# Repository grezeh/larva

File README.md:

# larva
larva keyboard related sketches, materials, etc

# larva mk.2

Mk.3 options:

 Larva keyboard is designed as part of a personal platform for research 
of combined, adaptable, extended latin+cyrillic keymap and layout with better ergonomics for day-to-day use.

 Keyboards, keymap, layouts are developed concurrently, work in symbiosis.
I name the whole research project "mnemoNИk|Kombine". 

 Larva PCB+custom plate fits in "daisy40% hhkb" keyboard case by Kprepublic.
Larva mk1 has 4 through-hole LED positions, no rgb, uses *AU mcu.

Mk2 has in addition 2 rgb smd LED slots for up-facing SK6812MINI-E LEDs 
and 2 pre-assembled mono-color smd LEDs as alternative to 2 lower through-hole LEDs(facedown, was an experimental feature)
and a few small QoL improvements. 

Mk2.1-light version cuts rgb and goes open-source. Pcbs routed by MarvFPV

Mk.3 pcb outline made smaller, to additionally fit "poseidon40" case by kprepublic. Added one more bottom row option and total-non-stab option (without iso enter). Modded by JLW, according to my specs (will see after the proto-run, how were the assumptions).

Current software-side implementation consists of QMK/vial +custom Windows keymap (needs updating).

Default keymap is basic latin+ numpad keycodes (looks chaotic, but gives more possibilities to reprogam); top-mid led is programmed as Num.Lock and it's engaged (put your novelties there and light them up; engaged numlock enables better bottom row options).

 For activating the bootloader: press the RST button on the back of the pcb.

 (The keyboard design line is constantly evolving, can differ in shapes and sizes, but all serve the same ultimate goal.
 Current line consists of: Larva mk1\mk2\mk2.1\mk3; Katerpillar; Katerpillar Infiltrator; Wodka; Wolof; Dragonfly; Butterfly; Mothra; Stargate; Galaga mk.1\mk.2\mk.3; Boardstroll)

* Keyboard Maintainer: [grezeh](https://github.com/grezeh)
* Hardware Supported: *Larva mk.2 pcb (atmega32u4)*
* Hardware Availability: *discord, occasionally, maybe*

QMK hex file compilation for this keyboard (after setting up your build environment,in QMK SYS for Qmk Toolbox):

    qmk compile -kb grezeh/larva/larva2 -km default (compiles locally, needs to go upstream at one point)

VIAL hex file compilation:
    
	qmk compile -kb grezeh/larva/larva2 -km vial (compiles locally. from vial git repo- not with recent changes; need to investigate, what new they implemented)

See the [build environment setup](https://docs.qmk.fm/#/getting_started_build_tools)
 and the [make instructions](https://docs.qmk.fm/#/getting_started_make_guide) for more information.
 Brand new to QMK? Start with our [Complete Newbs Guide](https://docs.qmk.fm/#/newbs).
 
 ps: lately vial have been giving errors, but locally still compiles fine. needs investigating
  (also, rgb is borked in current version- was experimental feature anyway, cut in version 2.1-light)
  
  oktoberfest'22- open sause the thing! 
  
  (now need to make "house in order", so noone brakes legs here. will upload simplified keymap later. Basically: need to upload qmk and vial files here, in addition to keymap)
  
  feedback on possible schematics flaws/improvements is appreciated

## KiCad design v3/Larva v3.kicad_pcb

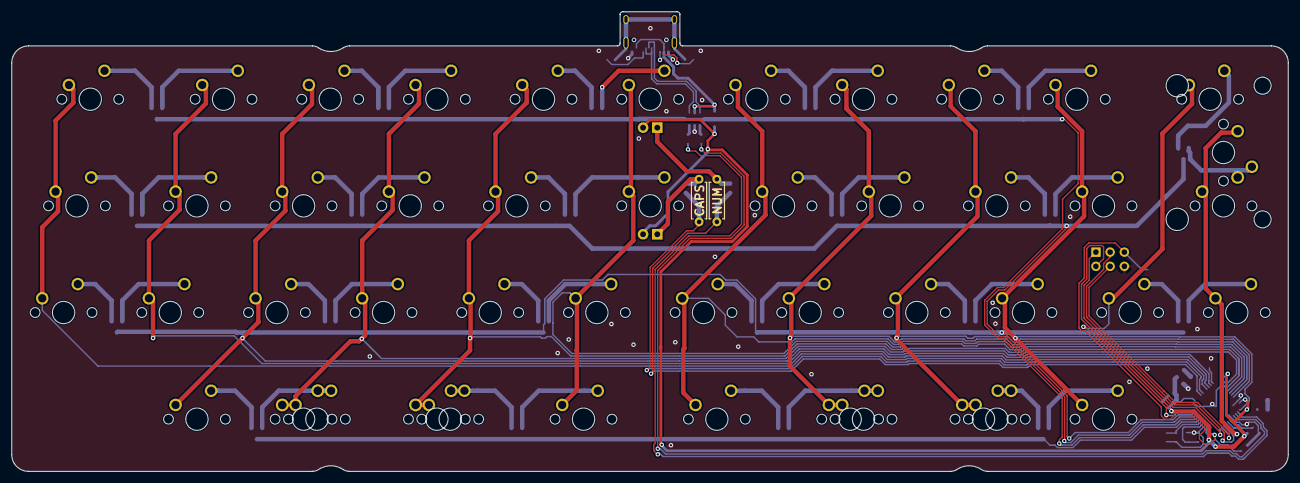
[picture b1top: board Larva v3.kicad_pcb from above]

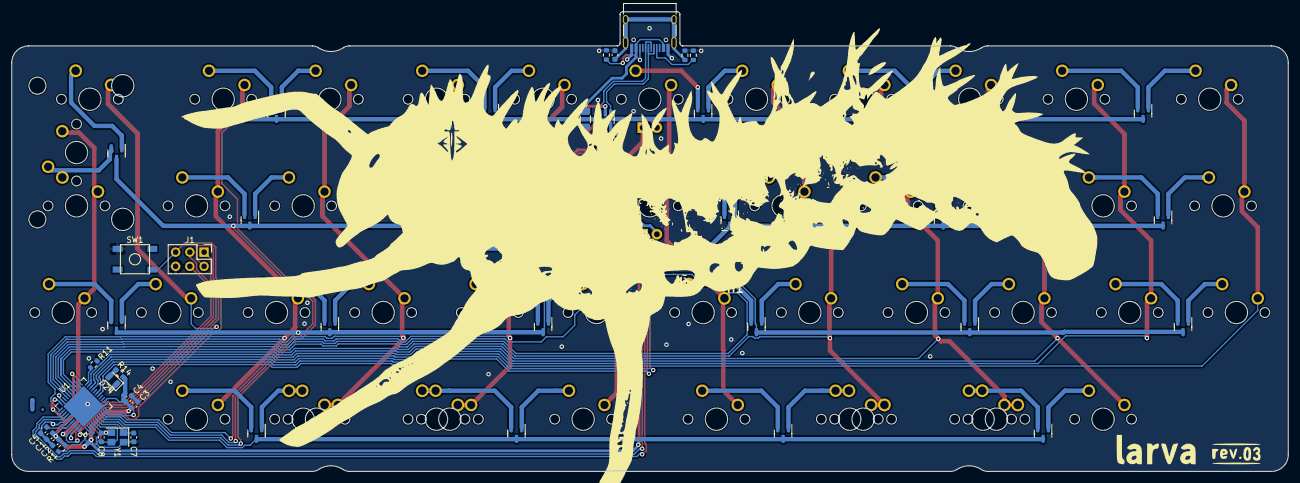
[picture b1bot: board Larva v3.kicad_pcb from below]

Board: 2 copper layers, 228.0 x 82.1 mm, 98 parts (49 on the bottom side), 83 nets.

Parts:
C1, C2, C3: 0.1uF; C_0603_1608Metric
C4: 10uF; C_0603_1608Metric
C5: 1uF; C_0603_1608Metric
C6: 100nF; C_0603_1608Metric
C7, C8: 22pF; C_0603_1608Metric
D1, D2, D3, D4, D5, D6, D7, D8, D9, D10, D11, D12, D13, D14, D15, D16, D17, D19, D20, D21, D22: BAT54C; SOT-23
D24: LED; LED_0805_2012Metric
F1: 500mA; Fuse_1206_3216Metric
H1: MountingHole; larvalogo3
H2: MountingHole; larvasidelines
J1: Conn_02x03_Odd_Even; PinHeader_2x03_P2.54mm_Vertical
J2: USB_C_Receptacle_USB2.0; USB_C_Receptacle_HRO_TYPE-C-31-M-12
MX1: MX-NoLED; MXOnly-1.5U-NoLED
MX2, MX3, MX4, MX5, MX7, MX8, MX9, MX10, MX12, MX13, MX14, MX15, MX17, MX18, MX19, MX20, MX22, MX23, MX24, MX25, MX26, MX29, MX30, MX31, MX32, MX33, MX34, MX41: MX-NoLED; MXOnly-1U-NoLED
MX6: MX-LED; MXOnly-1U
MX11, MX35, MX36, MX37, MX38, MX39, MX40: MX-NoLED; MXOnly-1.25U-NoLED
MX16: MX-LED; MXOnly-1.5U
MX21: MX-NoLED; MXOnly-ISO-ROTATED-ReversedStabilizers-NoLED
MX27, MX28: MX-LED; SW_MX_1u
MX42: MX-NoLED; SW_MX_1.25u
MX43, MX45, MX46: MX-NoLED; SW_MX_1.5u
MX44, MX47: MX-NoLED; SW_MX_1u
R1, R11: 10k; R_0603_1608Metric
R2, R3: 22; R_0603_1608Metric
R4, R5: 5.1k; R_0603_1608Metric
R7, R8: 680; R_0603_1608Metric
R10: 1M; R_0603_1608Metric
R12, R13: 680; R_Axial_DIN0207_L6.3mm_D2.5mm_P7.62mm_Horizontal
R14: 300; R_0603_1608Metric_Pad0.98x0.95mm_HandSolder
SW1: SW_Push; SKQG-1155865
U1: ATmega32U4-M; QFN-44-1EP_7x7mm_P0.5mm_EP5.2x5.2mm
U2: USBLC6-2SC6; SOT-23-6
Y1: Crystal_GND24_Small; Crystal_SMD_3225-4Pin_3.2x2.5mm

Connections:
+5V: C1.1, C2.1, C3.1, C4.1, F1.2, J1.2, MX6.3 (LED), MX16.3 (LED), R1.1, R14.1, U1.2 (UVCC), U1.7 (VBUS), U1.14 (VCC), U1.24 (AVCC), U1.34 (VCC), U1.44 (AVCC)
/Col0: MX1.1 (COL), MX11.1 (COL), MX22.1 (COL), U1.30 (PB6)
/Col1: MX2.1 (COL), MX12.1 (COL), MX23.1 (COL), U1.31 (PC6)
/Col2: MX3.1 (COL), MX13.1 (COL), MX24.1 (COL), MX34.1 (COL), U1.32 (PC7)
/Col3: MX4.1 (COL), MX14.1 (COL), MX25.1 (COL), MX35.1 (COL), MX44.1 (COL), U1.36 (PF7)
/Col4: MX5.1 (COL), MX15.1 (COL), MX26.1 (COL), MX36.1 (COL), MX45.1 (COL), U1.37 (PF6)
/Col5: MX6.1 (COL), MX16.1 (COL), MX27.1 (COL), MX37.1 (COL), U1.38 (PF5)
/Col6: MX7.1 (COL), MX17.1 (COL), MX28.1 (COL), MX38.1 (COL), U1.39 (PF4)
/Col7: MX8.1 (COL), MX18.1 (COL), MX29.1 (COL), MX39.1 (COL), MX46.1 (COL), U1.40 (PF1)
/Col8: MX9.1 (COL), MX19.1 (COL), MX30.1 (COL), MX40.1 (COL), MX47.1 (COL), U1.41 (PF0)
/Col9: MX10.1 (COL), MX20.1 (COL), MX31.1 (COL), MX41.1 (COL), U1.1 (PE6)
/Col10: MX32.1 (COL), MX43.1 (COL), U1.22 (PD5)
/Col11: MX21.1 (COL), MX33.1 (COL), MX42.1 (COL), U1.8 (PB0)
/D+: R2.2, U2.1 (I/O1)
/D-: R3.2, U2.3 (I/O2)
/LED0: MX6.4 (LEDGND), R8.1, R12.1
/LED1: MX16.4 (LEDGND), R7.1, R13.1
/LED_MID: R7.2, R13.2, U1.28 (PB4)
/LED_TOP: R8.2, R12.2, U1.27 (PD7)
/MISO: J1.1, U1.11 (PB3)
/MOSI: J1.4, U1.10 (PB2)
/RST: J1.5, R1.2, SW1.1, U1.13 (~RESET)
/Row0: D1.3, D2.3, D3.3, D4.3, D5.3, U1.19 (PD1)
/Row1: D6.3, D7.3, D8.3, D9.3, D10.3, D11.3, U1.20 (PD2)
/Row2: D12.3, D13.3, D14.3, D15.3, D16.3, D17.3, U1.21 (PD3)
/Row3: D19.3, D20.3, D21.3, D22.3, U1.18 (PD0)
/SCK: J1.3, U1.9 (PB1)
/USBD+: J2.A6 (D+), J2.B6 (D+), U2.6 (I/O1)
/USBD-: J2.A7 (D-), J2.B7 (D-), U2.4 (I/O2)
GND: C1.2, C2.2, C3.2, C4.2, C5.2, C6.2, C7.2, C8.1, D24.1 (K), J1.6, J2.A1 (GND), J2.A12 (GND), J2.B1 (GND), J2.B12 (GND), R4.1, R5.2, R10.1, R11.2, SW1.2, U1.5 (UGND), U1.15 (GND), U1.23 (GND), U1.35 (GND), U1.43 (GND), U1.45 (GND), U2.2 (GND), Y1.2, Y1.4
unnamed: D24.2 (A), R14.2
unnamed: J2.A5 (CC1), R4.2
unnamed: J2.B5 (CC2), R5.1
unnamed: C6.1, J2.S1 (SHIELD), R10.2
unnamed: D1.1, MX1.2 (ROW)
unnamed: D1.2, MX2.2 (ROW)
unnamed: D2.1, MX3.2 (ROW)
unnamed: D2.2, MX4.2 (ROW)
unnamed: D3.1, MX5.2 (ROW)
unnamed: D3.2, MX6.2 (ROW)
unnamed: D4.1, MX7.2 (ROW)
unnamed: D4.2, MX8.2 (ROW)
unnamed: D5.1, MX9.2 (ROW)
unnamed: D5.2, MX10.2 (ROW)
unnamed: D6.1, MX11.2 (ROW)
unnamed: D6.2, MX12.2 (ROW)
unnamed: D7.1, MX13.2 (ROW)
unnamed: D7.2, MX14.2 (ROW)
unnamed: D8.1, MX15.2 (ROW)
unnamed: D8.2, MX16.2 (ROW)
unnamed: D9.1, MX17.2 (ROW)
unnamed: D9.2, MX18.2 (ROW)
unnamed: D10.1, MX19.2 (ROW)
unnamed: D10.2, MX20.2 (ROW)
unnamed: D11.2, MX21.2 (ROW), MX42.2 (ROW)
unnamed: D12.1, MX22.2 (ROW)
unnamed: D12.2, MX23.2 (ROW)
unnamed: D13.1, MX24.2 (ROW)
unnamed: D13.2, MX25.2 (ROW)
unnamed: D14.1, MX26.2 (ROW)
unnamed: D14.2, MX27.2 (ROW)
unnamed: D15.1, MX28.2 (ROW)
unnamed: D15.2, MX29.2 (ROW)
unnamed: D16.1, MX30.2 (ROW)
unnamed: D16.2, MX31.2 (ROW)
unnamed: D17.1, MX32.2 (ROW)
unnamed: D17.2, MX33.2 (ROW)
unnamed: D19.1, MX34.2 (ROW)
unnamed: D19.2, MX35.2 (ROW), MX44.2 (ROW)
unnamed: D20.1, MX36.2 (ROW), MX45.2 (ROW)
unnamed: D20.2, MX37.2 (ROW)
unnamed: D21.1, MX38.2 (ROW)
unnamed: D21.2, MX39.2 (ROW), MX46.2 (ROW)
unnamed: D22.1, MX40.2 (ROW), MX47.2 (ROW)
unnamed: D22.2, MX41.2 (ROW)
unnamed: D11.1, MX43.2 (ROW)
unnamed: R2.1, U1.4 (D+)
unnamed: R3.1, U1.3 (D-)
unnamed: C5.1, U1.6 (UCAP)
unnamed: C7.1, U1.17 (XTAL1), Y1.1
unnamed: C8.2, U1.16 (XTAL2), Y1.3
unnamed: R11.1, U1.33 (~HWB/PE2)
VCC: F1.1, J2.A4 (VBUS), J2.A9 (VBUS), J2.B4 (VBUS), J2.B9 (VBUS), U2.5 (VBUS)

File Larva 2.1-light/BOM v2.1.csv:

Comment,Designator,Footprint,LCSC Part Number
680,"R9,R6,R8,R7",R_0603_1608Metric,C23228
smd2,D23,LED_0603_1608Metric,C89811
smd1,D18,LED_0603_1608Metric,C375444
500mA,F1,Fuse_1206_3216Metric,C69688 
SK6812MINI,"D25,D24",SK6812MINI-E,
Crystal_GND24_Small,Y1,Crystal_SMD_3225-4Pin_3.2x2.5mm,C13738
22pF,"C8,C7",C_0603_1608Metric,C1653
ATmega32U4-AU,U1,TQFP-44_10x10mm_P0.8mm,C44854 
USB_C_Receptacle_USB2.0,J2,USB_C_Receptacle_HRO_TYPE-C-31-M-12,C165948 
USBLC6-2SC6,U2,SOT-23-6,C7519
SW_Push,RST,SKQG-1155865,C318884
10k,"R11,R1",R_0603_1608Metric,C25804
1M,R10,R_0603_1608Metric,C269705 
5.1k,"R5,R4",R_0603_1608Metric,C23186
22,"R3,R2",R_0603_1608Metric,C23345
BAT54C,"D22,D21,D20,D19,D17,D16,D15,D14,D13,D12,D11,D10,D9,D8,D7,D6,D5,D4,D3,D2,D1",SOT-23,C14308
1uF,C5,C_0603_1608Metric,C15849
10uF,C4,C_0603_1608Metric,C19702
0.1uF,"C3,C2,C1,C10,C9,C6",C_0603_1608Metric,C14663

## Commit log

2021-02-20 Add files via upload
    Larva keyboard initial layout/sketch
2021-02-22 Add files via upload
    Latin script half of Mnemonic layout, adapted for Larva keyboard. (half-mnemonic simplified)
2021-02-22 Add files via upload
    latin half of Mnemonic layout, ad Larva
2021-02-22 Add files via upload
    mnemoNИk on Larva, initial. (working on it still)
2021-02-22 Add files via upload
    mnemoNИк layout on Larva, wip (KLE)
2021-02-22 Add files via upload
    mnemoNИk layout on Larva. wip (KLE)
2021-02-22 Add files via upload
    mnemoNИk layout, adapted for Larva. ver 02
2021-02-22 Add files via upload
    mnemoNИk layout on Larva. (wip KLE)
2021-02-26 Add files via upload
    latin half of Mnemonic layout, adf Larva
2022-10-06 Add files via upload
    open sause
2022-10-06 simplified plate, no kerf [fur laserboost]
2022-10-06 simplified latin keymap + KLE raw
2022-10-07 Delete simplified keymap.png
    need to edit
2022-10-07 default keymap (simplified, basic latin)
2022-10-08 dæfault basic keymap, subject to change
2022-10-08 mnæmoNИк хаоѕ layout
2022-10-08 mnæmoNИк хаоѕ layout KLE raw
2022-10-08 simplified basic keymap [update]
2022-10-08 mnæmoNИк (tяu xaos) layout update
2023-12-20 started v3 work
2024-01-11 update LEDs
2024-02-29 larva mk.3 layout options
2024-05-05 larva3 plate, universal, top-mount for Daisy
    larva3 plate, top-mount for Daisy. (not yet tested)
